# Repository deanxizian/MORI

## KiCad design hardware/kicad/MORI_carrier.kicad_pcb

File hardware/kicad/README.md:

# MORI 原生 KiCad 工程

实际工具 **KiCad10.0.6**。入口 `MORI_carrier.kicad_pro`，同名.kicad_sch/.kicad_pcb；工程本地符号库、所需封装子集、库表、connectivity.json和carrier_bom.csv齐备。接口符号用真实针号和功能电气类型表示远端模块；自定义矩形不是芯片厂商符号外形，但网络与封装焊盘是真实原生对象。模块内部电路由原厂模块实现，见wiring.csv，不把载板当成完全集成设计。

76个载板封装（包含4安装孔及11测试点），模块连接口、看门狗、AND门、编码器电平转换、母线吸能/采样/USB隔离具体到引脚。原理图本地网名经KiCad原生导出，生成PCB时按导出的针脚网络赋值并逐针交叉核验。空置IC输出NC，未用输入固定电平；两个电源标志只说明SS34/急停NC外部供电路径，不能作为真正电源器件。

板框对应98×94平台内部，外接尺寸96×92、截角、孔中心Blender(±40,±42)，NPTH3.4。PCB(x,y)=(BlenderX+100, BlenderY+100)，PCB高度候选117；上视/下视和世界坐标不要混淆。舵机槽x[-38,-6]/y[-12,12]，线孔(14,±7)Ø10。元件已作粗布局，但没有按电流回路/噪声/天线/热细化，也未证明三维安装。

**UNROUTED / NOT FOR FABRICATION**：无走线、无铜区、无Gerber或钻孔生产文件。DRC必须报告未连接；不得通过忽略未连接规则把状态改成PASS。A0原理图适合在KiCad放大查看，另有SVG预览；电源与功能概览见architecture.md。

```sh
cd /Users/dean/Documents/MORI
python3 hardware/tools/create_design.py
/Applications/KiCad/KiCad.app/Contents/Frameworks/Python.framework/Versions/Current/bin/python3 hardware/tools/generate_kicad.py
/Applications/KiCad/KiCad.app/Contents/MacOS/kicad-cli sch erc hardware/kicad/MORI_carrier.kicad_sch --format json -o hardware/reports/erc.json
/Applications/KiCad/KiCad.app/Contents/MacOS/kicad-cli pcb drc hardware/kicad/MORI_carrier.kicad_pcb --format json --schematic-parity -o hardware/reports/drc.json
```

CLI在本机可能输出Fontconfig/wx无GUI警告；是否成功按退出码、能重新加载的原生文件与报告判断，保留原始日志。ERC通过仅表示当前功能引脚规则；不检查外部线束实际电平/方向、封装真实样品、热、锂电安全和闭环稳定。

下一版布局：VM电容/吸能开关靠近DRV VMM；驱动与降压模块高di/dt环小；ADC RC贴近ADC连接端并远离H桥/天线；U1/U2/U5去耦贴电源脚；两电机电流回流不经IMU返回；地连续；ESP天线按厂家规范禁铜/禁金属并露出板边；模块引线短且成对，所有针1和极性在丝印可辨。放行前用实际模块3D模型核验高度/插拔和±65°头扫掠。

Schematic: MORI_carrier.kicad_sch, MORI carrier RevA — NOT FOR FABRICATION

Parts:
C1: 1uF_50V_X7R; C_0805_2012Metric
C2, C3, C4, C5, C6, C13: 100nF; C_0805_2012Metric
C7: 100nF_25V; C_0805_2012Metric
C8: 1nF_C0G; C_0805_2012Metric
C9: 1000uF_16V; CP_Radial_D10.0mm_P5.00mm
C10: 470uF_10V; CP_Radial_D10.0mm_P5.00mm
C11: 100uF_10V; CP_Radial_D10.0mm_P5.00mm
C12: 100uF_16V; CP_Radial_D10.0mm_P5.00mm
D1: SS34_USB_ISOLATION; D_SMA
H1, H2, H3, H4: M3_deck_hole_3.4mm; MountingHole_3.4mm_M3
J1: VMAIN_from_protected_pack; TerminalBlock_Phoenix_MKDS-1,5-2_1x02_P5.00mm_Horizontal
J2: DevKit_v1.1_N8R8_HARNESS; IDC-Header_2x13_P2.54mm_Vertical
J3: DRV8833_Pololu2130_HARNESS; JST_XH_B14B-XH-A_1x14_P2.50mm_Vertical
J4, J5: Motor4863_CUSTOM_XH6; JST_XH_B6B-XH-A_1x06_P2.50mm_Vertical
J6: Adafruit4438_IMU; JST_XH_B5B-XH-A_1x05_P2.50mm_Vertical
J7: INA219_LOGIC; JST_SH_BM04B-SRSS-TB_1x04-1MP_P1.00mm_Vertical
J8: INA219_SHUNT_IN_OUT; TerminalBlock_Phoenix_MKDS-1,5-2_1x02_P5.00mm_Horizontal
J9: Waveshare19192_LCD; JST_PH_B8B-PH-K_1x08_P2.00mm_Vertical
J10: SER0037_JR_GND_5V_SIGNAL; PinHeader_1x03_P2.54mm_Vertical
J11: ESTOP_2NC_EXTERNAL; JST_VH_B4P-VH_1x04_P3.96mm_Vertical
J12: BUCK_LOGIC_UNPLUG_FOR_USB; JST_XH_B3B-XH-A_1x03_P2.50mm_Vertical
J13: BUCK_SERVO_D24V22F5; JST_XH_B3B-XH-A_1x03_P2.50mm_Vertical
J14: DevKit_5V_KEEP_FOR_ENCODERS; JST_XH_B2B-XH-A_1x02_P2.50mm_Vertical
J15, J16: 10k_B3380_ON_MOTOR; JST_XH_B2B-XH-A_1x02_P2.50mm_Vertical
J17: DUMP_RESISTOR_HS25_5R6J; TerminalBlock_Phoenix_MKDS-1,5-2_1x02_P5.00mm_Horizontal
Q1: IRLZ44NPBF_DUMP; TO-220-3_Vertical
R1, R2, R3, R4, R5: 10k; R_0805_2012Metric
R6: 47k; R_0805_2012Metric
R7: 30k_1pct; R_0805_2012Metric
R8, R10, R11: 10k_1pct; R_0805_2012Metric
R9, R12, R13: 1k; R_0805_2012Metric
R14: 25k5_0.1pct; R_0805_2012Metric
R15: 10k_0.1pct; R_0805_2012Metric
R16: 2M2_1pct; R_0805_2012Metric
R17: 2k2; R_0805_2012Metric
R18: 4k7; R_0805_2012Metric
R19: 100R; R_0805_2012Metric
R20, R21, R22, R23, R24: 100k; R_0805_2012Metric
TP1: GND; TestPoint_Pad_D1.5mm
TP2: VMAIN; TestPoint_Pad_D1.5mm
TP3: VM_MOTOR; TestPoint_Pad_D1.5mm
TP4: DEVKIT_5V; TestPoint_Pad_D1.5mm
TP5: 3V3; TestPoint_Pad_D1.5mm
TP6: ARM; TestPoint_Pad_D1.5mm
TP7: WD_OK; TestPoint_Pad_D1.5mm
TP8: NSLEEP; TestPoint_Pad_D1.5mm
TP9: NFAULT; TestPoint_Pad_D1.5mm
TP10: BUS_DIV; TestPoint_Pad_D1.5mm
TP11: CLAMP_OUT; TestPoint_Pad_D1.5mm
U1: CD74HC123E; DIP-16_W7.62mm
U2: SN74HC08N; DIP-14_W7.62mm
U3: LM393P; DIP-8_W7.62mm
U4: TL431BCLP; TO-92_Inline
U5: SN74LVC14AD; SOIC-14_3.9x8.7mm_P1.27mm

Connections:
/3V3: C2.1, C3.1, C13.1, J2.25 (3V3), J6.1 (3V3), J7.2 (3V3), J9.1 (3V3), J9.8 (3V3), J11.1 (3V3), R4.1, R6.1, R10.1, R11.1, TP5.1, U1.16 (VCC), U2.14 (VCC), U5.14 (VCC)
/AIN1: J2.4 (AIN1), J3.4 (AIN1)
/AIN2: J2.5 (AIN2), J3.5 (AIN2)
/ARM: J2.18 (ARM), R1.1, TP6.1, U1.3 (1CLR), U2.1 (1A)
/ARM_WD: U2.3 (1Y), U2.4 (2A)
/BAT_ADC: C4.1, J2.1 (BAT_ADC), R9.2
/BAT_DIV: R7.2, R8.1, R9.1
/BIN1: J2.6 (BIN1), J3.6 (BIN1)
/BIN2: J2.7 (BIN2), J3.7 (BIN2)
/BUS_DIV: C8.1, R14.2, R15.1, R16.2, TP10.1, U3.3 (IN1+)
/CLAMP_OUT: R16.1, R18.2, R19.1, TP11.1, U3.1 (OUT1)
/DEVKIT_5V: D1.1 (K), J4.4 (VCC), J5.4 (VCC), J14.1 (DEVKIT_5V), TP4.1
/DUMP_DRAIN: J17.2 (DUMP_DRAIN), Q1.2 (D)
/DUMP_GATE: Q1.1 (G), R19.2, R20.1
/ENC_LA: J2.8 (ENC_LA), U5.2 (1Y)
/ENC_LA_5V: J4.3 (A), R21.1, U5.1 (1A)
/ENC_LB: J2.9 (ENC_LB), U5.4 (2Y)
/ENC_LB_5V: J4.2 (B), R22.1, U5.3 (2A)
/ENC_RA: J2.10 (ENC_RA), U5.6 (3Y)
/ENC_RA_5V: J5.3 (A), R23.1, U5.5 (3A)
/ENC_RB: J2.11 (ENC_RB), U5.8 (4Y)
/ENC_RB_5V: J5.2 (B), R24.1, U5.9 (4A)
/ESTOP_OK: J2.24 (ESTOP_OK), J11.2 (ESTOP_OK), R3.1, U2.5 (2B)
/GND: C2.2, C3.2, C4.2, C5.2, C6.2, C7.2, C8.2, C9.2 (-), C10.2 (-), C11.2 (-), C12.2 (-), C13.2, J1.2 (GND), J2.26 (GND), J3.3 (GND), J3.14 (GND), J4.1 (GND), J5.1 (GND), J6.2 (GND), J7.1 (GND), J9.2 (GND), J10.1 (GND), J12.2 (GND), J13.2 (GND), J14.2 (GND), J15.2 (GND), J16.2 (GND), Q1.3 (S), R1.2, R2.2, R3.2, R5.2, R8.2, R15.2, R20.2, R21.2, R22.2, R23.2, R24.2, TP1.1, U1.1 (1A), U1.8 (GND), U1.9 (2A), U1.10 (2B), U1.11 (2CLR), U2.7 (GND), U2.12 (4A), U2.13 (4B), U3.4 (V-), U3.5 (IN2+), U4.2 (A), U5.7 (GND), U5.11 (5A), U5.13 (6A)
/HEAD_5V: J10.2 (HEAD_5V), J11.4 (HEAD_5V)
/HEAD_PWM: J2.21 (HEAD_PWM), J10.3 (HEAD_PWM)
/HEARTBEAT: J2.22 (HEARTBEAT), R2.1, U1.2 (1B)
/IMU_INT: J2.15 (IMU_INT), J6.5 (IMU_INT)
/LCD_CLK: J2.13 (LCD_CLK), J9.4 (LCD_CLK)
/LCD_CS: J2.14 (LCD_CS), J9.5 (LCD_CS)
/LCD_DC: J2.19 (LCD_DC), J9.6 (LCD_DC)
/LCD_MOSI: J2.12 (LCD_MOSI), J9.3 (LCD_MOSI)
/LCD_RST: J2.20 (LCD_RST), J9.7 (LCD_RST)
/LM1: J3.10 (LM1), J4.6 (M1)
/LM2: J3.11 (LM2), J4.5 (M2)
/LOGIC_5V_RAW: C11.1 (+), D1.2 (A), J12.3 (LOGIC_5V_RAW)
/NFAULT: J2.23 (NFAULT), J3.9 (NFAULT), R4.2, TP9.1, U2.10 (3B)
/NSLEEP: J3.8 (NSLEEP), R5.1, TP8.1, U2.8 (3Y)
/NTC_L: C5.1, J2.2 (NTC_L), R12.2
/NTC_L_RAW: J15.1 (NTC_L_RAW), R10.2, R12.1
/NTC_R: C6.1, J2.3 (NTC_R), R13.2
/NTC_R_RAW: J16.1 (NTC_R_RAW), R11.2, R13.1
/RM1: J3.12 (RM1), J5.6 (M1)
/RM2: J3.13 (RM2), J5.5 (M2)
/RUN_OK: U2.6 (2Y), U2.9 (3A)
/SCL: J2.17 (SCL), J6.4 (SCL), J7.4 (SCL)
/SDA: J2.16 (SDA), J6.3 (SDA), J7.3 (SDA)
/SERVO_5V_RAW: C10.1 (+), J11.3 (SERVO_5V_RAW), J13.3 (SERVO_5V_RAW)
/VMAIN: C12.1 (+), J1.1 (VMAIN), J8.1 (VMAIN), J12.1 (VMAIN), J13.1 (VMAIN), R7.1, TP2.1
/VM_DRV_IN: J3.1 (VM_DRV_IN), J8.2 (VM_DRV_IN)
/VM_MOTOR: C7.1, C9.1 (+), J3.2 (VM_MOTOR), J17.1 (VM_MOTOR), R14.1, R17.1, R18.1, TP3.1, U3.8 (V+)
/VREF_2V495: R17.2, U3.2 (IN1-), U3.6 (IN2-), U4.1 (REF), U4.3 (K)
/WD_C: C1.1, U1.14 (1C)
/WD_OK: TP7.1, U1.13 (1Q), U2.2 (1B)
/WD_RC: C1.2, R6.2, U1.15 (1RC)

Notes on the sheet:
MORI RevA — PROTOTYPE / UNVALIDATED — module harness + safety circuitry; see wiring.csv for offboard paths

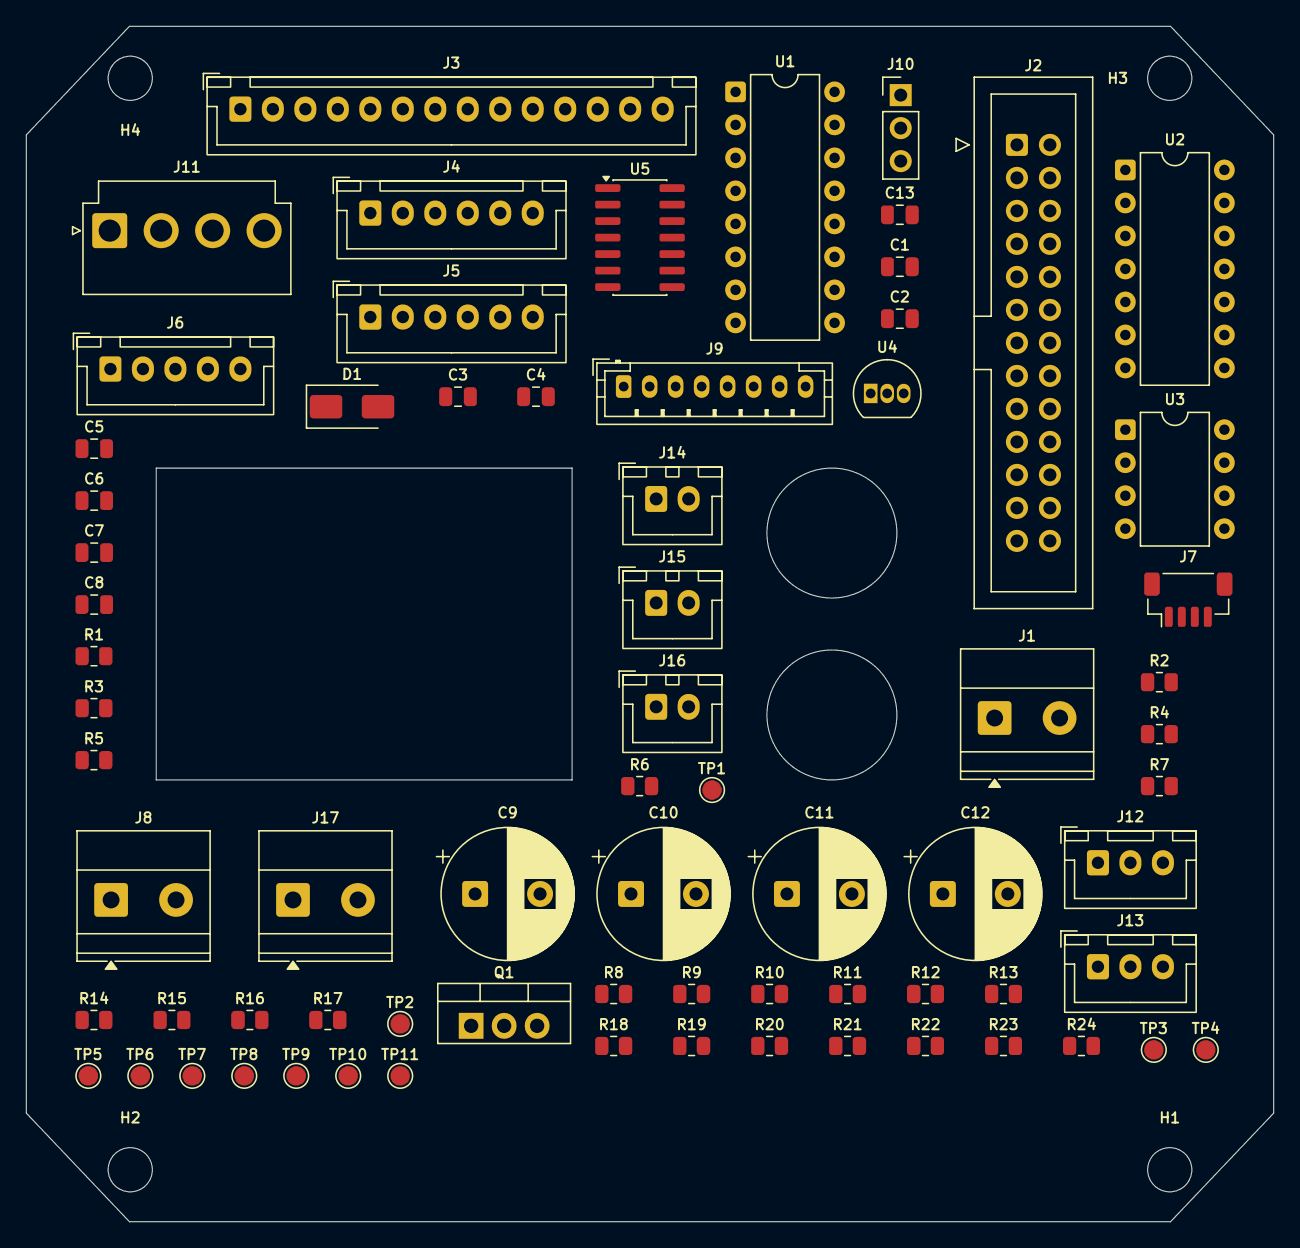
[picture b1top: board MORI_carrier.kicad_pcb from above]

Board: 2 copper layers, 96.0 x 92.0 mm, 76 parts (0 on the bottom side), 55 nets, no tracks yet.

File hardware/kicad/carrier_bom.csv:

ref,value,footprint,section,note
J1,VMAIN_from_protected_pack,"TerminalBlock_Phoenix:TerminalBlock_Phoenix_MKDS-1,5-2_1x02_P5.00mm_Horizontal",POWER,
J2,DevKit_v1.1_N8R8_HARNESS,Connector_IDC:IDC-Header_2x13_P2.54mm_Vertical,IO,Remote board represented with functional pin directions
J3,DRV8833_Pololu2130_HARNESS,Connector_JST:JST_XH_B14B-XH-A_1x14_P2.50mm_Vertical,IO,
J4,Motor4863_CUSTOM_XH6,Connector_JST:JST_XH_B6B-XH-A_1x06_P2.50mm_Vertical,IO,CUSTOM retermination:1 green GND;2 white B;3 yellow A;4 blue Vcc 5V;5 black M2;6 red M1. NOT factory header order. LVC14 level shifts required.
J5,Motor4863_CUSTOM_XH6,Connector_JST:JST_XH_B6B-XH-A_1x06_P2.50mm_Vertical,IO,CUSTOM retermination:1 green GND;2 white B;3 yellow A;4 blue Vcc 5V;5 black M2;6 red M1. NOT factory header order. LVC14 level shifts required.
J6,Adafruit4438_IMU,Connector_JST:JST_XH_B5B-XH-A_1x05_P2.50mm_Vertical,IO,
J7,INA219_LOGIC,Connector_JST:JST_SH_BM04B-SRSS-TB_1x04-1MP_P1.00mm_Vertical,IO,
J8,INA219_SHUNT_IN_OUT,"TerminalBlock_Phoenix:TerminalBlock_Phoenix_MKDS-1,5-2_1x02_P5.00mm_Horizontal",POWER,
J9,Waveshare19192_LCD,Connector_JST:JST_PH_B8B-PH-K_1x08_P2.00mm_Vertical,IO,
J10,SER0037_JR_GND_5V_SIGNAL,Connector_PinHeader_2.54mm:PinHeader_1x03_P2.54mm_Vertical,IO,
J11,ESTOP_2NC_EXTERNAL,Connector_JST:JST_VH_B4P-VH_1x04_P3.96mm_Vertical,SAFETY,
J12,BUCK_LOGIC_UNPLUG_FOR_USB,Connector_JST:JST_XH_B3B-XH-A_1x03_P2.50mm_Vertical,POWER,UNPLUG whole J12 logic-buck harness before USB; manufacturer power modes mutually exclusive. Keep J14 connected so USB also supplies encoder 5V. Battery may power motors/head separately.
J13,BUCK_SERVO_D24V22F5,Connector_JST:JST_XH_B3B-XH-A_1x03_P2.50mm_Vertical,POWER,
J14,DevKit_5V_KEEP_FOR_ENCODERS,Connector_JST:JST_XH_B2B-XH-A_1x02_P2.50mm_Vertical,POWER,KEEP J14 connected in both supply modes: DevKit 5V and encoder bus. Disconnect J12 logic buck before USB; do not cut encoder power by unplugging J14.
J15,10k_B3380_ON_MOTOR,Connector_JST:JST_XH_B2B-XH-A_1x02_P2.50mm_Vertical,IO,
J16,10k_B3380_ON_MOTOR,Connector_JST:JST_XH_B2B-XH-A_1x02_P2.50mm_Vertical,IO,
J17,DUMP_RESISTOR_HS25_5R6J,"TerminalBlock_Phoenix:TerminalBlock_Phoenix_MKDS-1,5-2_1x02_P5.00mm_Horizontal",CLAMP,
U1,CD74HC123E,Package_DIP:DIP-16_W7.62mm,SAFETY,
U2,SN74HC08N,Package_DIP:DIP-14_W7.62mm,SAFETY,
U5,SN74LVC14AD,Package_SO:SOIC-14_3.9x8.7mm_P1.27mm,ENCODER,
C13,100nF,Capacitor_SMD:C_0805_2012Metric,ENCODER,
U3,LM393P,Package_DIP:DIP-8_W7.62mm,CLAMP,
U4,TL431BCLP,Package_TO_SOT_THT:TO-92_Inline,CLAMP,
Q1,IRLZ44NPBF_DUMP,Package_TO_SOT_THT:TO-220-3_Vertical,CLAMP,
D1,SS34_USB_ISOLATION,Diode_SMD:D_SMA,POWER,
R1,10k,Resistor_SMD:R_0805_2012Metric,SAFETY,
R2,10k,Resistor_SMD:R_0805_2012Metric,SAFETY,
R3,10k,Resistor_SMD:R_0805_2012Metric,SAFETY,
R4,10k,Resistor_SMD:R_0805_2012Metric,SAFETY,
R5,10k,Resistor_SMD:R_0805_2012Metric,SAFETY,
R6,47k,Resistor_SMD:R_0805_2012Metric,SAFETY,
R7,30k_1pct,Resistor_SMD:R_0805_2012Metric,ADC,
R8,10k_1pct,Resistor_SMD:R_0805_2012Metric,ADC,
R9,1k,Resistor_SMD:R_0805_2012Metric,ADC,
R10,10k_1pct,Resistor_SMD:R_0805_2012Metric,ADC,
R11,10k_1pct,Resistor_SMD:R_0805_2012Metric,ADC,
R12,1k,Resistor_SMD:R_0805_2012Metric,ADC,
R13,1k,Resistor_SMD:R_0805_2012Metric,ADC,
R14,25k5_0.1pct,Resistor_SMD:R_0805_2012Metric,CLAMP,
R15,10k_0.1pct,Resistor_SMD:R_0805_2012Metric,CLAMP,
R16,2M2_1pct,Resistor_SMD:R_0805_2012Metric,CLAMP,
R17,2k2,Resistor_SMD:R_0805_2012Metric,CLAMP,
R18,4k7,Resistor_SMD:R_0805_2012Metric,CLAMP,
R19,100R,Resistor_SMD:R_0805_2012Metric,CLAMP,
R20,100k,Resistor_SMD:R_0805_2012Metric,CLAMP,
R21,100k,Resistor_SMD:R_0805_2012Metric,ENCODER,
R22,100k,Resistor_SMD:R_0805_2012Metric,ENCODER,
R23,100k,Resistor_SMD:R_0805_2012Metric,ENCODER,
R24,100k,Resistor_SMD:R_0805_2012Metric,ENCODER,
C1,1uF_50V_X7R,Capacitor_SMD:C_0805_2012Metric,DECOUPLING,
C2,100nF,Capacitor_SMD:C_0805_2012Metric,DECOUPLING,
C3,100nF,Capacitor_SMD:C_0805_2012Metric,DECOUPLING,
C4,100nF,Capacitor_SMD:C_0805_2012Metric,DECOUPLING,
C5,100nF,Capacitor_SMD:C_0805_2012Metric,DECOUPLING,
C6,100nF,Capacitor_SMD:C_0805_2012Metric,DECOUPLING,
C7,100nF_25V,Capacitor_SMD:C_0805_2012Metric,DECOUPLING,
C8,1nF_C0G,Capacitor_SMD:C_0805_2012Metric,DECOUPLING,
C9,1000uF_16V,Capacitor_THT:CP_Radial_D10.0mm_P5.00mm,POWER,
C10,470uF_10V,Capacitor_THT:CP_Radial_D10.0mm_P5.00mm,POWER,
C11,100uF_10V,Capacitor_THT:CP_Radial_D10.0mm_P5.00mm,POWER,
C12,100uF_16V,Capacitor_THT:CP_Radial_D10.0mm_P5.00mm,POWER,
TP1,GND,TestPoint:TestPoint_Pad_D1.5mm,TESTPOINT,
TP2,VMAIN,TestPoint:TestPoint_Pad_D1.5mm,TESTPOINT,
TP3,VM_MOTOR,TestPoint:TestPoint_Pad_D1.5mm,TESTPOINT,
TP4,DEVKIT_5V,TestPoint:TestPoint_Pad_D1.5mm,TESTPOINT,
TP5,3V3,TestPoint:TestPoint_Pad_D1.5mm,TESTPOINT,
TP6,ARM,TestPoint:TestPoint_Pad_D1.5mm,TESTPOINT,
TP7,WD_OK,TestPoint:TestPoint_Pad_D1.5mm,TESTPOINT,
TP8,NSLEEP,TestPoint:TestPoint_Pad_D1.5mm,TESTPOINT,
TP9,NFAULT,TestPoint:TestPoint_Pad_D1.5mm,TESTPOINT,
TP10,BUS_DIV,TestPoint:TestPoint_Pad_D1.5mm,TESTPOINT,
TP11,CLAMP_OUT,TestPoint:TestPoint_Pad_D1.5mm,TESTPOINT,
H1,M3_deck_hole_3.4mm,MORI_Mech:MountingHole_3.4mm_M3,MECHANICAL,"copied deck XY, standoff Z pending"
H2,M3_deck_hole_3.4mm,MORI_Mech:MountingHole_3.4mm_M3,MECHANICAL,"copied deck XY, standoff Z pending"
H3,M3_deck_hole_3.4mm,MORI_Mech:MountingHole_3.4mm_M3,MECHANICAL,"copied deck XY, standoff Z pending"
H4,M3_deck_hole_3.4mm,MORI_Mech:MountingHole_3.4mm_M3,MECHANICAL,"copied deck XY, standoff Z pending"

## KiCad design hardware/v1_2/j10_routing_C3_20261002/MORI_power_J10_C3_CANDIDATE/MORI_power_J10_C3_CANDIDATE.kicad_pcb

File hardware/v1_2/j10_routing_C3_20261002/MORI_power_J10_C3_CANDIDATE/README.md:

# MORI power J10-C3 独立候选

已布通，原生 ERC/DRC 为零；未完成真实装配/热/动力测试，未正式发布。

请从 [候选总览](../README.md) 和 [布线复核](../ROUTING_REVIEW.md) 阅读真实检查及阻断项。不要使用 C2 的历史检查来描述 C3。

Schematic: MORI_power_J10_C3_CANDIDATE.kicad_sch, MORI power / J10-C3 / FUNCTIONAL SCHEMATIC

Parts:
C1, C20: 100n; C_0603_1608Metric
C2: 1u 25V; C_0603_1608Metric__P3_C2
C10: Panasonic EEU-FR1C102 1000uF 16V; CP_Radial_D10.0mm_P5.00mm__P2_C10__P3_C10__P5_C10
C21, C41: 10n; C_0603_1608Metric
C30: Panasonic EEU-FR1C102 1000uF 16V; CP_Radial_D10.0mm_P5.00mm__P3_C30__P5_C30
C40: 100n; C_0603_1608Metric__P5_C40
C60: 22u / 25V / X7R; C_1210_3225Metric__P3_C60__P3R1_C60
C61: 100n / 50V / X7R; C_0603_1608Metric__P5_C61
C62, C72: 100n / 50V / X7R; C_0603_1608Metric
C63: 22u / 25V / X7R; C_1210_3225Metric__P5_C63
C64, C66, C73, C76: 22u / 25V / X7R; C_1210_3225Metric
C65: 75p / 50V / C0G; C_0603_1608Metric__P5_C65
C70: 22u / 25V / X7R; C_1210_3225Metric__P3_C70
C71: 100n / 50V / X7R; C_0603_1608Metric__P5_C71
C74: 22u / 25V / X7R; C_1210_3225Metric__P3_C74
C75: 75p / 50V / C0G; C_0603_1608Metric__P3R1_C75
D1, D20, D90: BZT52H-C10,115; D_SOD-123F
D10: B540C-13-F; D_SMC__P3_D10__P5_D10
D30: B540C-13-F; D_SMC__P5_D30
D40: BZT52H-C10,115; D_SOD-123F__P5_D40
F60: 1A / 125V / very fast; Fuse_Littelfuse-NANO2-451_453
F70: 2A / 125V / very fast; Fuse_Littelfuse-NANO2-451_453__P5_F70
H1, H2, H3, H4: M2 mounting / POSITION TBD; MountingHole_2.2mm_M2
J1: PACK AFTER 6.3A FUSE; AMASS_XT30UPB-M_1x02_P5.0mm_Vertical__P3_J1
J2: WHEEL BUCK VIN; AMASS_XT30UPB-M_1x02_P5.0mm_Vertical__P3_J2__P5_J2
J3: WHEEL BUCK 9V RETURN; AMASS_XT30UPB-M_1x02_P5.0mm_Vertical__P3R1_J3
J4: HEAD BUCK VIN; AMASS_XT30UPB-M_1x02_P5.0mm_Vertical__P2_J4__P3_J4__P3R1_J4
J5: HEAD BUCK 6V RETURN; AMASS_XT30UPB-M_1x02_P5.0mm_Vertical__P2_J5__P3_J5__P5_J5
J6: BAT_MON SERVICE / DNP; AMASS_XT30UPB-M_1x02_P5.0mm_Vertical__P3_J6__P3R1_J6; not fitted
J7: S288 L; JST_XH_B3B-XH-A_1x03_P2.50mm_Vertical__P2_J7__P3_J7__P5_J7
J8: S288 R; JST_XH_B3B-XH-A_1x03_P2.50mm_Vertical__P2_J8__P5_J8
J9: SCS0009 CHAIN; JST_XH_B3B-XH-A_1x03_P2.50mm_Vertical__P5_J9
J10: MOTION CONTROL; JST_PH_S8B-PH-K_1x08_P2.00mm_Horizontal__C2_land1p50_finish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
J11: WHEEL DUMP 5R6 EXTERNAL; AMASS_XT30UPB-M_1x02_P5.0mm_Vertical__P5R5_DUMP
J12: HEAD DUMP 10R EXTERNAL; AMASS_XT30UPB-M_1x02_P5.0mm_Vertical__P2_J12__P5_J12__P5R5_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
J13: S288 DATA; JST_PH_B2B-PH-K_1x02_P2.00mm_Vertical__P4_PH_ANNULUS
J14: HEAD DATA; JST_PH_B3B-PH-K_1x03_P2.00mm_Vertical__P4_PH_ANNULUS
J15: CHARGE INTERLOCK; JST_PH_B2B-PH-K_1x02_P2.00mm_Vertical__P4_PH_ANNULUS__P3R1_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
J16: CHARGER RAW VBUS SENSE; JST_PH_B2B-PH-K_1x02_P2.00mm_Vertical__P4_PH_ANNULUS__P3R1_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
J17: MOTION 5V OUT / 1+ 2GND; JST_PH_B2B-PH-K_1x02_P2.00mm_Vertical__P4_PH_ANNULUS
J18: CAM 5V OUT / 1+ 2GND; JST_XH_B2B-XH-A_1x02_P2.50mm_Vertical
J19: REAR MASTER / 1RETURN 2GND; JST_PH_B2B-PH-K_1x02_P2.00mm_Vertical__P4_PH_ANNULUS__P5_J19
JP60: SERVICE OFF / OPEN=ON; PinHeader_1x02_P2.54mm_Vertical__P3_JP60__P3R1_JP60
JP70: SERVICE OFF / OPEN=ON; PinHeader_1x02_P2.54mm_Vertical__P5_JP70
L60, L70: 10uH / SRP7050TA-100M; Bourns_SRP7050TA_8p4_span_2p5_gap
Q1: AO4407A; SOIC-8_3.9x4.9mm_P1.27mm__P5_Q1
Q10, Q90: AO4407A; SOIC-8_3.9x4.9mm_P1.27mm
Q11: AO3400A; SOT-23__P5_Q11
Q20, Q31, Q40: AO3400A; SOT-23
Q30: AO4407A; SOIC-8_3.9x4.9mm_P1.27mm__P5_Q30
Q50: MMBT3904LT1G; SOT-23__P5_Q50
R1, R30, R91: 10k; R_0603_1608Metric
R2: WSL2512R0100FEA 10mR 1% 1W; R_2512_6332Metric
R3, R4: 0; R_0603_1608Metric
R10: 10k; R_0603_1608Metric__P5_R10
R11: 100; R_0603_1608Metric__P5_R11
R20, R24, R40, R44: 2.2k; R_0603_1608Metric
R21: 33.2k 0.1%; R_0603_1608Metric
R22: 10k 0.1%; R_0603_1608Metric__P5_R22
R23, R43: 1M 0.1%; R_0603_1608Metric
R25: 37.4k 0.1%; R_0603_1608Metric
R26, R42, R46: 10k 0.1%; R_0603_1608Metric
R31: 100; R_0603_1608Metric__P5_R31
R41: 16.5k 0.1%; R_0603_1608Metric
R45: 18.7k 0.1%; R_0603_1608Metric__P5_R45
R50, R52: 100k 0.1%; R_0603_1608Metric
R51, R53: 27k 0.1%; R_0603_1608Metric
R54: 10k; R_0603_1608Metric__P5_R54
R55: 47k; R_0603_1608Metric
R56: 100k; R_0603_1608Metric__P5_R56
R60, R70: 100k / 0.1%; R_0603_1608Metric
R61: 13.3k / 0.1%; R_0603_1608Metric
R71: 13.3k / 0.1%; R_0603_1608Metric__P3_R71
R90: 100k; R_0603_1608Metric
TP60: +5V_MOTION; TestPoint_Pad_D1.5mm__P3_TP60
TP61: GND; TestPoint_Pad_D1.5mm__P5_TP61
TP70: +5V_CAM; TestPoint_Pad_D1.5mm__P3R1_TP70
TP71: GND; TestPoint_Pad_D1.5mm__P5_TP71
U1: INA180A1IDBVR; SOT-23-5__P5_U1
U20: LM393BDR; SOIC-8_3.9x4.9mm_P1.27mm__P5_U20
U21: TL431BIDBZR; SOT-23
U40: LM393BDR; SOIC-8_3.9x4.9mm_P1.27mm__P5_U40
U41: TL431BIDBZR; SOT-23__P5_U41
U60, U70: TPS54302DDCR; TI_DDC0006A_TPS54302

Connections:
/+3V3: C1.1, J10.1, U1.5 (VS)
/+5V_CAM: C73.1, C74.1, C75.1, J18.1 (5V_OUT), L70.2, R70.1, TP70.1
/+5V_MOTION: C63.1, C64.1, C65.1, J17.1 (5V_OUT), L60.2, R60.1, TP60.1
/ARM_Q: J10.2, Q11.1, Q31.1, R54.1
/BAT_ADC: J10.5, R50.2, R51.1
/BAT_IN: Q1.5, Q1.6, Q1.7, Q1.8, Q90.5, Q90.6, Q90.7, Q90.8
/BAT_MON: C2.1, F60.1, F70.1, J2.2 (PLUS), J4.2 (PLUS), J6.2 (PLUS), R2.2, R4.1, R50.1
/BAT_REV: D1.1, Q1.1 (SOURCE PROTECTED OUTPUT), Q1.2, Q1.3, R2.1, R3.1
/C5_BOOT: C72.1, U70.6 (BOOT)
/C5_EN: JP70.1 (EN), U70.5 (EN)
/C5_FB: C75.2, R70.2, R71.1, U70.4 (FB)
/C5_SW: C72.2, L70.1, U70.2 (SW)
/C5_VIN: C70.1, C71.1, C76.1, F70.2, U70.3 (VIN)
/CHG_BASE: Q50.1 (B), R55.2, R56.1
/CHG_N: J10.4, J15.1, Q50.3 (C)
/CURRENT_ADC: J10.7, U1.1 (OUT)
/FAULT_N: J10.3, U20.7 (OUT2), U40.7 (OUT2)
/GND: C1.2, C2.2, C10.2, C20.2, C21.2, C30.2, C40.2, C41.2, C60.2, C61.2, C63.2, C64.2, C66.2, C70.2, C71.2, C73.2, C74.2, C76.2, D20.2, D40.2, J1.1 (MINUS), J2.1 (MINUS), J3.1 (MINUS), J4.1 (MINUS), J5.1 (MINUS), J6.1 (MINUS), J7.1 (GND), J8.1 (GND), J9.1 (GND), J10.8, J13.2, J14.2, J15.2, J16.2, J17.2 (GND), J18.2 (GND), J19.2, JP60.2 (GND), JP70.2 (GND), Q11.2, Q20.2, Q31.2, Q40.2, Q50.2 (E), R1.2, R22.2, R26.2, R42.2, R46.2, R51.2, R53.2, R54.2, R56.2, R61.2, R71.2, TP61.1, TP71.1, U1.2 (GND), U20.4 (GND), U21.3 (A), U40.4 (GND), U41.3 (A), U60.1 (GND), U70.1 (GND)
/H6_IN: D30.2, J5.2 (PLUS)
/H_BRAKE_GATE: D40.1, Q40.1, R43.1, R44.2, U40.1 (OUT1)
/H_BUS: J9.3 (BUS), J14.1
/H_DUMP_D: J12.1 (MINUS), Q40.3
/H_GATE: Q30.4, R30.1, R31.1
/H_GATE_LOW: Q31.3, R31.2
/H_OVSENSE: C41.1, R45.2, R46.1, U40.6 (IN2-)
/H_PRE: D30.1, Q30.1, Q30.2, Q30.3, R30.2
/H_REF: R40.2, U40.2 (IN1-), U40.5 (IN2+), U41.1 (K), U41.2 (REF)
/H_SENSE: R41.2, R42.1, R43.2, U40.3 (IN1+)
/H_VM: C30.1, C40.1, J9.2 (V+), J12.2 (PLUS), Q30.5 (DRAIN SWITCHED OUTPUT), Q30.6, Q30.7, Q30.8, R40.1, R41.1, R44.1, R45.1, U40.8 (VCC)
/KELVIN_N: R4.2, U1.4 (IN-)
/KELVIN_P: R3.2, U1.3 (IN+)
/M5_BOOT: C62.1, U60.6 (BOOT)
/M5_EN: JP60.1 (EN), U60.5 (EN)
/M5_FB: C65.2, R60.2, R61.1, U60.4 (FB)
/M5_SW: C62.2, L60.1, U60.2 (SW)
/M5_VIN: C60.1, C61.1, C66.1, F60.2, U60.3 (VIN)
/MASTER_GATE: D90.2, Q90.4, R90.2, R91.1
/MASTER_RETURN: J19.1, R91.2
/PACK_FUSED: D90.1, J1.2 (PLUS), Q90.1, Q90.2, Q90.3, R90.1
/REV_GATE: D1.2, Q1.4, R1.1
/VBUS_CHARGE: J16.1, R55.1
/W9_IN: D10.2, J3.2 (PLUS)
/WHEEL_ADC: J10.6, R52.2, R53.1
/W_BRAKE_GATE: D20.1, Q20.1, R23.1, R24.2, U20.1 (OUT1)
/W_BUS: J7.3 (BUS), J8.3 (BUS), J13.1
/W_DUMP_D: J11.1 (MINUS), Q20.3
/W_GATE: Q10.4, R10.1, R11.1
/W_GATE_LOW: Q11.3, R11.2
/W_OVSENSE: C21.1, R25.2, R26.1, U20.6 (IN2-)
/W_PRE: D10.1, Q10.1, Q10.2, Q10.3, R10.2
/W_REF: R20.2, U20.2 (IN1-), U20.5 (IN2+), U21.1 (K), U21.2 (REF)
/W_SENSE: R21.2, R22.1, R23.2, U20.3 (IN1+)
/W_VM: C10.1, C20.1, J7.2 (V+), J8.2 (V+), J11.2 (PLUS), Q10.5 (DRAIN SWITCHED OUTPUT), Q10.6, Q10.7, Q10.8, R20.1, R21.1, R24.1, R25.1, R52.1, U20.8 (VCC)

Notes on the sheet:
MORI / POWER CONDITIONER / P4
Power flows left to right. Supplies above, returns below. PROTOTYPE / UNVALIDATED.
01 Pack input / reverse protection / shunt
Q90 master stage precedes BAT_IN. No charger on this PCB.
10mR / 1% / 1W
02 Kelvin current sense
Sense from the shunt pads. Discharge-only nominal transfer: 0.2 V/A.
03 Wheel 9 V conditioning
External buck return. Inrush, brake energy and thermal performance: NOT_TESTED.
1000u / 16V
04 Head 6 V conditioning
05 External converter input distribution
J2: wheel buck. J4: head buck. J6: BAT_MON SERVICE / DNP.
06 Wheel rail / brake and overvoltage
Two comparators share one LM393B. External dump resistor needs pulse qualification.
LM393B / brake + fault
5R6 / 5W external
07 Head rail / brake and overvoltage
10R / 5W external
08 Voltage monitor / motion connector
Divider ratio 27 / 127. Current_ADC comes from block 02.
09 Charge insertion / VBUS sense
Sense and interlock only; no CC / PD / CC-CV charger implementation.
10 Supply boundaries / board mounting
80 x 55 mm PCB; populated assembly and thermal performance are not qualified.
Supply boundary
11 Motion 5 V / independent fused buck
Prototype: verify stability, temperature, cable drop and concurrent load. No PCB placement frozen.
1A input fuse
22u/25V
100n
100n BOOT
10uH / 4A rms
MOTION 5V
100k 0.1%
13.3k 0.1%
75p C0G
OPEN=ON / SHORT=OFF
5V probe
GND probe

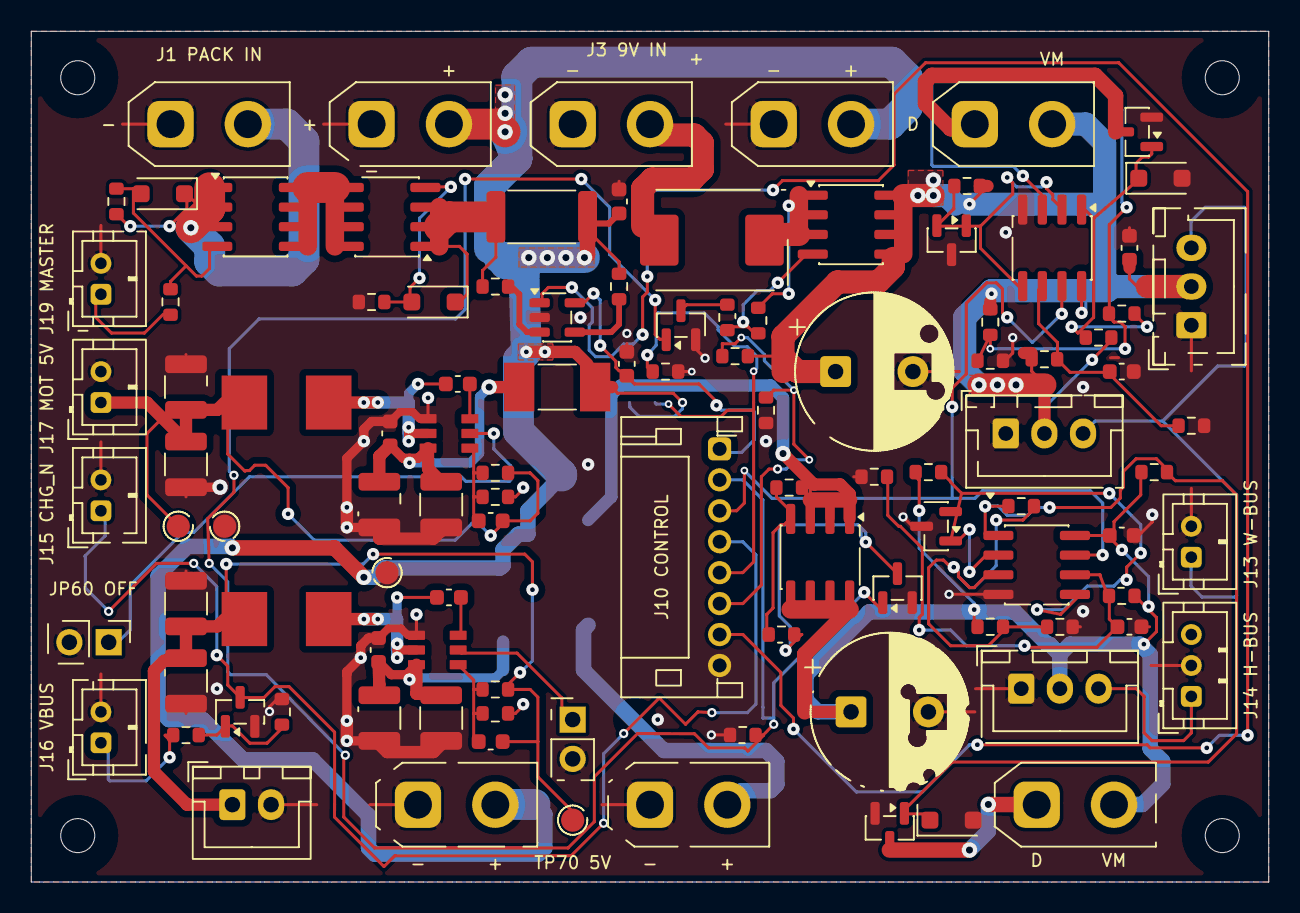
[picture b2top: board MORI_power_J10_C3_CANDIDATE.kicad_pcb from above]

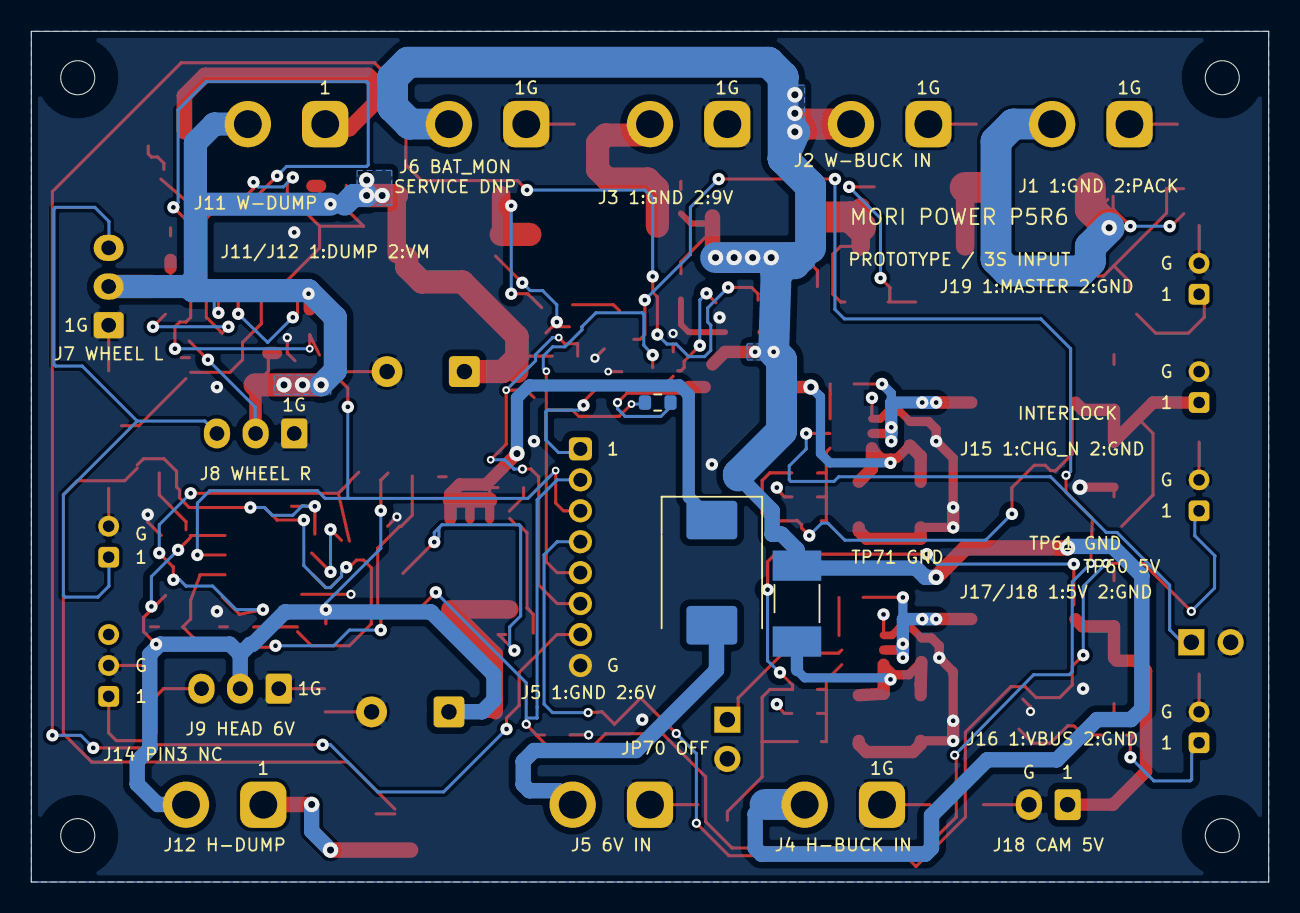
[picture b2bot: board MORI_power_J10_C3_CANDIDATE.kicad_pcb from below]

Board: 4 copper layers, 80.0 x 55.0 mm, 112 parts (3 on the bottom side), 53 nets.

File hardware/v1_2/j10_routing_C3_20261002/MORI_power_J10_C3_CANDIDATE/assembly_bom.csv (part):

ref,value,footprint,source,note
J1,PACK AFTER 6.3A FUSE,MORI_Custom:AMASS_XT30UPB-M_1x02_P5.0mm_Vertical__P3_J1,,Protected finished3S pack through external6.3A fuse. On-board Q90 is controlled by rear SW1. No direct small-switch load current.
J2,WHEEL BUCK VIN,MORI_Custom:AMASS_XT30UPB-M_1x02_P5.0mm_Vertical__P3_J2__P5_J2,,"AMASS XT30UPB-M PCB: pin1 minus, pin2 plus; mating housing polarization plus continuity check mandatory."
J3,WHEEL BUCK 9V RETURN,MORI_Custom:AMASS_XT30UPB-M_1x02_P5.0mm_Vertical__P3R1_J3,,"AMASS XT30UPB-M PCB: pin1 minus, pin2 plus; mating housing polarization plus continuity check mandatory."
J4,HEAD BUCK VIN,MORI_Custom:AMASS_XT30UPB-M_1x02_P5.0mm_Vertical__P2_J4__P3_J4__P3R1_J4,,"AMASS XT30UPB-M PCB: pin1 minus, pin2 plus; mating housing polarization plus continuity check mandatory."
J5,HEAD BUCK 6V RETURN,MORI_Custom:AMASS_XT30UPB-M_1x02_P5.0mm_Vertical__P2_J5__P3_J5__P5_J5,,"AMASS XT30UPB-M PCB: pin1 minus, pin2 plus; mating housing polarization plus continuity check mandatory."
J6,BAT_MON SERVICE / DNP,MORI_Custom:AMASS_XT30UPB-M_1x02_P5.0mm_Vertical__P3_J6__P3R1_J6,,Legacy external5V feed no longer used. Not5V. Leave unpopulated in S3.
J11,WHEEL DUMP 5R6 EXTERNAL,MORI_Custom:AMASS_XT30UPB-M_1x02_P5.0mm_Vertical__P5R5_DUMP,,"AMASS XT30UPB-M PCB: pin1 minus, pin2 plus; mating housing polarization plus continuity check mandatory."
J12,HEAD DUMP 10R EXTERNAL,MORI_Custom:AMASS_XT30UPB-M_1x02_P5.0mm_Vertical__P2_J12__P5_J12__P5R5_DUMP,,"AMASS XT30UPB-M PCB: pin1 minus, pin2 plus; mating housing polarization plus continuity check mandatory."
J7,S288 L,MORI_Custom:JST_XH_B3B-XH-A_1x03_P2.50mm_Vertical__P2_J7__P3_J7__P5_J7,,Board-side XH 3-pin interface only. SCS original 5264-3P uses 1GND/2VCC/3TTL. S288 factory mating plug remains unverified; adapter harness must be confirmed.
J8,S288 R,MORI_Custom:JST_XH_B3B-XH-A_1x03_P2.50mm_Vertical__P2_J8__P5_J8,,Board-side XH 3-pin interface only. SCS original 5264-3P uses 1GND/2VCC/3TTL. S288 factory mating plug remains unverified; adapter harness must be confirmed.
J9,SCS0009 CHAIN,MORI_Custom:JST_XH_B3B-XH-A_1x03_P2.50mm_Vertical__P5_J9,,Board-side XH 3-pin interface only. SCS original 5264-3P uses 1GND/2VCC/3TTL. S288 factory mating plug remains unverified; adapter harness must be confirmed.
J10,MOTION CONTROL,Connector_JST:JST_PH_S8B-PH-K_1x08_P2.00mm_Horizontal__C2_land1p50_finished0p90,https://www.jst-mfg.com/product/pdf/eng/ePH.pdf,P4 PH 2.0 mm. PHR-8 / SPH-002T-P0.5S. Signal pin numbering unchanged. Check both mating views; never wire by color alone.
J13,S288 DATA,MORI_Custom:JST_PH_B2B-PH-K_1x02_P2.00mm_Vertical__P4_PH_ANNULUS,https://www.jst-mfg.com/product/pdf/eng/ePH.pdf,P4 PH 2.0 mm. PHR-2 / SPH-002T-P0.5S. Signal pin numbering unchanged. Check both mating views; never wire by color alone.
J14,HEAD DATA,MORI_Custom:JST_PH_B3B-PH-K_1x03_P2.00mm_Vertical__P4_PH_ANNULUS,https://www.jst-mfg.com/product/pdf/eng/ePH.pdf,P4 PH 2.0 mm. PHR-3 / SPH-002T-P0.5S. Signal pin numbering unchanged. Check both mating views; never wire by color alone.
J15,CHARGE INTERLOCK,MORI_Custom:JST_PH_B2B-PH-K_1x02_P2.00mm_Vertical__P4_PH_ANNULUS__P3R1_J15,https://www.jst-mfg.com/product/pdf/eng/ePH.pdf,P4 PH 2.0 mm. PHR-2 / SPH-002T-P0.5S. Signal pin numbering unchanged. Check both mating views; never wire by color alone.
J16,CHARGER RAW VBUS SENSE,MORI_Custom:JST_PH_B2B-PH-K_1x02_P2.00mm_Vertical__P4_PH_ANNULUS__P3R1_J16,https://www.jst-mfg.com/product/pdf/eng/ePH.pdf,P4 PH 2.0 mm. PHR-2 / SPH-002T-P0.5S. Signal pin numbering unchanged. Check both mating views; never wire by color alone.
Q1,AO4407A,MORI_Custom:SOIC-8_3.9x4.9mm_P1.27mm__P5_Q1,https://www.aosmd.com/sites/default/files/res/datasheets/AO4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,
R1,10k,Resistor_SMD:R_0603_1608Metric,,
D1,"BZT52H-C10,115",Diode_SMD:D_SOD-123F,,
R2,WSL2512R0100FEA 10mR 1% 1W,Resistor_SMD:R_2512_6332Metric,,
U1,INA180A1IDBVR,MORI_Custom:SOT-23-5__P5_U1,https://www.ti.com/lit/ds/symlink/ina180.pdf,Kelvin sense of 10mR; gain20 =>0.2V/A. Discharge only; reverse current not measured.
R3,0,Resistor_SMD:R_0603_1608Metric,,
R4,0,Resistor_SMD:R_0603_1608Metric,,
D10,B540C-13-F,MORI_Custom:D_SMC__P3_D10__P5_D10,https://www.diodes.com/datasheet/download/B540C.pdf,B540C-13-F verified from DS13012 Rev18-2; SMC cathode pin1. Thermal/quote NOT_QUALIFIED.
Q10,AO4407A,Package_SO:SOIC-8_3.9x4.9mm_P1.27mm,https://www.aosmd.com/sites/default/files/res/datasheets/AO4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,
Q11,AO3400A,MORI_Custom:SOT-23__P5_Q11,https://www.aosmd.com/sites/default/files/res/datasheets/AO3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,
R10,10k,MORI_Custom:R_0603_1608Metric__P5_R10,,
R11,100,MORI_Custom:R_0603_1608Metric__P5_R11,,
C10,Panasonic EEU-FR1C102 1000uF 16V,MORI_Custom:CP_Radial_D10.0mm_P5.00mm__P2_C10__P3_C10__P5_C10,,"D10 x H16; height is vendor capacitor envelope, NOT fitted into old10mm allocation."
D30,B540C-13-F,MORI_Custom:D_SMC__P5_D30,https://www.diodes.com/datasheet/download/B540C.pdf,B540C-13-F verified from DS13012 Rev18-2; SMC cathode pin1. Thermal/quote NOT_QUALIFIED.
Q30,AO4407A,MORI_Custom:SOIC-8_3.9x4.9mm_P1.27mm__P5_Q30,https://www.aosmd.com/sites/default/files/res/datasheets/AO4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,
Q31,AO3400A,Package_TO_SOT_SMD:SOT-23,https://www.aosmd.com/sites/default/files/res/datasheets/AO3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,
R30,10k,Resistor_SMD:R_0603_1608Metric,,
R31,100,MORI_Custom:R_0603_1608Metric__P5_R31,,
C30,Panasonic EEU-FR1C102 1000uF 16V,MORI_Custom:CP_Radial_D10.0mm_P5.00mm__P3_C30__P5_C30,,"D10 x H16; height is vendor capacitor envelope, NOT fitted into old10mm allocation."
U20,LM393BDR,MORI_Custom:SOIC-8_3.9x4.9mm_P1.27mm__P5_U20,https://www.ti.com/lit/ds/symlink/lm393b.pdf,
U21,TL431BIDBZR,Package_TO_SOT_SMD:SOT-23,https://www.ti.com/lit/ds/symlink/tl431.pdf,"DBZ pin1 cathode,2 reference,3 anode. B grade +/-0.5% at25C; thermal error in tolerance model."
Q20,AO3400A,Package_TO_SOT_SMD:SOT-23,https://www.aosmd.com/sites/default/files/res/datasheets/AO3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,
D20,"BZT52H-C10,115",Diode_SMD:D_SOD-123F,,
R20,2.2k,Resistor_SMD:R_0603_1608Metric,,
R21,33.2k 0.1%,Resistor_SMD:R_0603_1608Metric,,
R22,10k 0.1%,MORI_Custom:R_0603_1608Metric__P5_R22,,
R23,1M 0.1%,Resistor_SMD:R_0603_1608Metric,,
R24,2.2k,Resistor_SMD:R_0603_1608Metric,,
R25,37.4k 0.1%,Resistor_SMD:R_0603_1608Metric,,
R26,10k 0.1%,Resistor_SMD:R_0603_1608Metric,,
C20,100n,Capacitor_SMD:C_0603_1608Metric,,
C21,10n,Capacitor_SMD:C_0603_1608Metric,,
U40,LM393BDR,MORI_Custom:SOIC-8_3.9x4.9mm_P1.27mm__P5_U40,https://www.ti.com/lit/ds/symlink/lm393b.pdf,
U41,TL431BIDBZR,MORI_Custom:SOT-23__P5_U41,https://www.ti.com/lit/ds/symlink/tl431.pdf,"DBZ pin1 cathode,2 reference,3 anode. B grade +/-0.5% at25C; thermal error in tolerance model."
Q40,AO3400A,Package_TO_SOT_SMD:SOT-23,https://www.aosmd.com/sites/default/files/res/datasheets/AO3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,
D40,"BZT52H-C10,115",MORI_Custom:D_SOD-123F__P5_D40,,
R40,2.2k,Resistor_SMD:R_0603_1608Metric,,
R41,16.5k 0.1%,Resistor_SMD:R_0603_1608Metric,,
R42,10k 0.1%,Resistor_SMD:R_0603_1608Metric,,
R43,1M 0.1%,Resistor_SMD:R_0603_1608Metric,,
R44,2.2k,Resistor_SMD:R_0603_1608Metric,,
R45,18.7k 0.1%,MORI_Custom:R_0603_1608Metric__P5_R45,,
R46,10k 0.1%,Resistor_SMD:R_0603_1608Metric,,
C40,100n,MORI_Custom:C_0603_1608Metric__P5_C40,,
C41,10n,Capacitor_SMD:C_0603_1608Metric,,
R50,100k 0.1%,Resistor_SMD:R_0603_1608Metric,,
R51,27k 0.1%,Resistor_SMD:R_0603_1608Metric,,
R52,100k 0.1%,Resistor_SMD:R_0603_1608Metric,,
R53,27k 0.1%,Resistor_SMD:R_0603_1608Metric,,
R54,10k,MORI_Custom:R_0603_1608Metric__P5_R54,,
R55,47k,Resistor_SMD:R_0603_1608Metric,,
R56,100k,MORI_Custom:R_0603_1608Metric__P5_R56,,
C1,100n,Capacitor_SMD:C_0603_1608Metric,,
C2,1u 25V,MORI_Custom:C_0603_1608Metric__P3_C2,,
Q50,MMBT3904LT1G,MORI_Custom:SOT-23__P5_Q50,,SOT23 1B 2E 3C. Raw VBUS detect only; neither CC nor charging control.
H1,M2 mounting / POSITION TBD,MountingHole:MountingHole_2.2mm_M2,,
H2,M2 mounting / POSITION TBD,MountingHole:MountingHole_2.2mm_M2,,
H3,M2 mounting / POSITION TBD,MountingHole:MountingHole_2.2mm_M2,,
H4,M2 mounting / POSITION TBD,MountingHole:MountingHole_2.2mm_M2,,
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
